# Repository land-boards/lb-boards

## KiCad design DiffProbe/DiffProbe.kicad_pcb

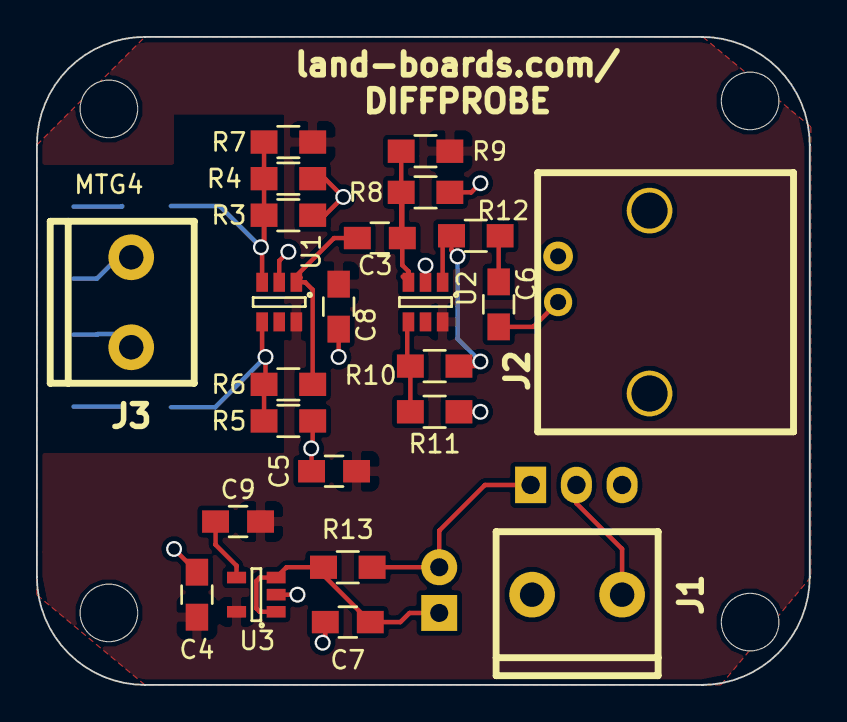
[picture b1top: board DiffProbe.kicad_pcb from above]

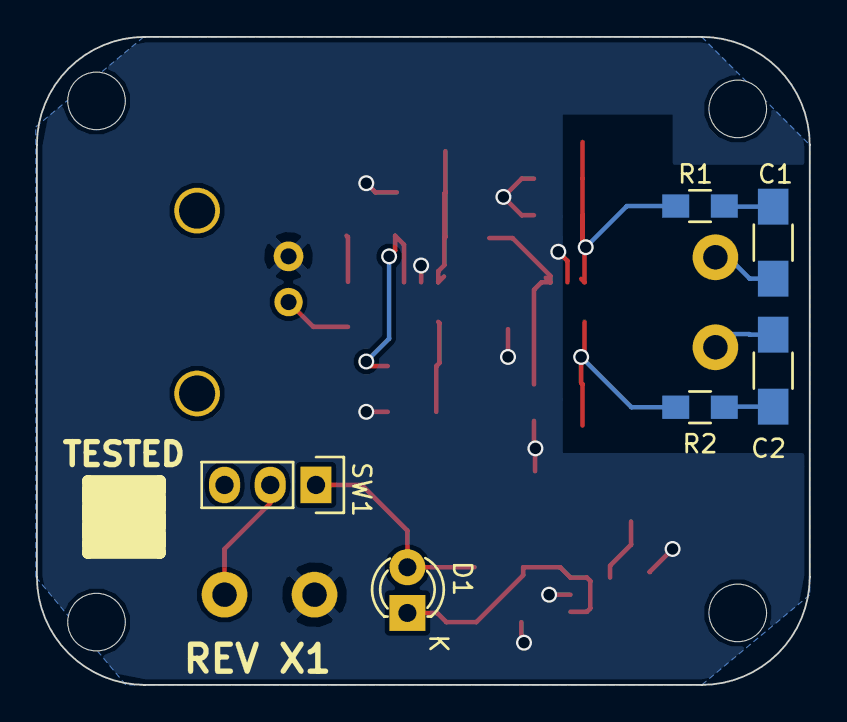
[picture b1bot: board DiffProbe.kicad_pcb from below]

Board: 2 copper layers, 42.9 x 36.0 mm, 35 parts (6 on the bottom side), 18 nets.

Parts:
C1, C2: 2.2nF/1kV; R_1206_HandSoldering
C3, C4, C5, C9: 10nF; C_0805_HandSoldering
C6, C7: 1uF; C_0805_HandSoldering
C8: 10uF; C_0805_HandSoldering
D1: LED; LED-3MM
J1, J3: CONN_01X02; TB2-5MM
J2: BNC; BNC-RT
MTG1, MTG2, MTG3, MTG4: MTG_HOLE; MountingHole_3.2mm_M3
R1, R2: 49.9K; R_0805_HandSoldering
R3, R5: 549; R_0805_HandSoldering
R4, R7, R8: 10K; R_0805_HandSoldering
R6: 4.99K; R_0805_HandSoldering
R9: 191K; R_0805_HandSoldering
R10: 499; R_0805_HandSoldering
R11: 54.9; R_0805_HandSoldering
R12: 48.7; R_0805_HandSoldering
R13: 75; R_0805_HandSoldering
SW1: SPST; Pin_Header_Straight_1x03
TESTED: TESTED_COUPON; TEST_BLK-REAR
U1, U2: LTC6268S6; SOT-23-6
U3: LT1761; SOT-23-5

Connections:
+5V: C4.1, C5.1, C8.1, C9.1, R7.2, R9.2, U1.6, U2.6, U3.5
GND: C4.2, C5.2, C7.2, C8.2, J1.2, J2.2, R3.2, R4.2, R5.1, R8.2, R11.1, U1.2, U2.2, U3.2
unnamed: C1.1, R1.2
unnamed: C1.2, J3.2
unnamed: C2.1, R2.2
unnamed: C2.2, J3.1
unnamed: C3.1, R8.1, R9.1, U2.3
unnamed: C3.2, R6.2, U1.1
unnamed: C6.1, J2.1
unnamed: C6.2, R12.2
unnamed: C7.1, D1.1, R13.1, U3.1, U3.3
unnamed: C9.2, U3.4
unnamed: D1.2, R13.2, SW1.1
unnamed: J1.1, SW1.2
unnamed: R1.1, R3.1, R4.1, R7.1, U1.3
unnamed: R2.1, R5.2, R6.1, U1.4
unnamed: R10.1, R11.2, U2.4
unnamed: R10.2, R12.1, U2.1

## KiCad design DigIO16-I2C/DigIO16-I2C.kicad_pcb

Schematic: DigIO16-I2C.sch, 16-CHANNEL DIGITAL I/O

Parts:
C1, C2: 0.1uF; C_Rect_L7_W2_P5
F1: FUSE; SM1206
FID1, FID2: ADAFRUIT_FIDUCIAL; FIDUCIAL
J1, J5: CONN_3; PIN_ARRAY_3X1
J2, J3: CONN_4; pin_array_4x1
J4: CONN_3X2; Pin_Header_Straight_2x03
J6: CONN_02X02; Pin_Header_Straight_2x02
J7: CONN_01X02; Pin_Header_Straight_1x02
J8: DB25; DB25FC
MTG1, MTG2, MTG3, MTG4: MTG_HOLE; MTG-6-32
R1, R2: 2.2K; R4-5
R3, R4, R6, R7, R8: 10K; R4-5
R5: 1K; R4-5
ST1, ST2: CONN_1; REV_BLOCK
U1: MCP23017P; DIP-28__300_ELL
U2: 24C01; DIP-8__300_ELL

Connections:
/A0: J4.6, R7.1, U1.15 (A0), U2.1 (A0)
/A1: J4.4, R8.1, U1.16 (A1), U2.2 (A1)
/A2: J4.2, R6.1, U1.17 (A2), U2.3 (A2)
/F5V: F1.2, J8.1, J8.2, J8.14
/INT: J5.2 (PM), R3.1, U1.20 (INTA)
/RST: R4.1, U1.18 (~RST)
/SCL: J2.4, J3.4, J6.4, U1.12 (SCL), U2.6 (SCL)
/SDA: J2.3, J3.3, J6.2, U1.13 (SDA), U2.5 (SDA)
/VCC: C1.1, C2.1, F1.1, J1.2 (PM), J2.2, J3.2, R1.2, R2.2, R3.2, R4.2, R5.2, R6.2, R7.2, R8.2, U1.9 (VDD), U2.8 (VCC)
GND: C1.2, C2.2, J1.1, J1.3, J2.1, J3.1, J4.1, J4.3, J4.5, J5.1, J5.3, J7.2, J8.7, J8.12, J8.13, J8.19, J8.20, J8.25, U1.10 (VSS), U2.4 (GND)
unnamed: J6.1, R1.1
unnamed: J6.3, R2.1
unnamed: J7.1, R5.1, U2.7 (TEST)
unnamed: J8.3, U1.27 (GPA6)
unnamed: J8.4, U1.25 (GPA4)
unnamed: J8.5, U1.23 (GPA2)
unnamed: J8.6, U1.21 (GPA0)
unnamed: J8.8, U1.1 (GPB0)
unnamed: J8.9, U1.3 (GPB2)
unnamed: J8.10, U1.5 (GPB4)
unnamed: J8.11, U1.7 (GPB6)
unnamed: J8.15, U1.28 (GPA7)
unnamed: J8.16, U1.26 (GPA5)
unnamed: J8.17, U1.24 (GPS3)
unnamed: J8.18, U1.22 (GPA1)
unnamed: J8.21, U1.2 (GPB1)
unnamed: J8.22, U1.4 (GPB3)
unnamed: J8.23, U1.6 (GPB5)
unnamed: J8.24, U1.8 (GPB7)

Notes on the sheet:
SCL SDA VCC GND
GND VCC GND
~CP ~INT GND
POWER
I2C

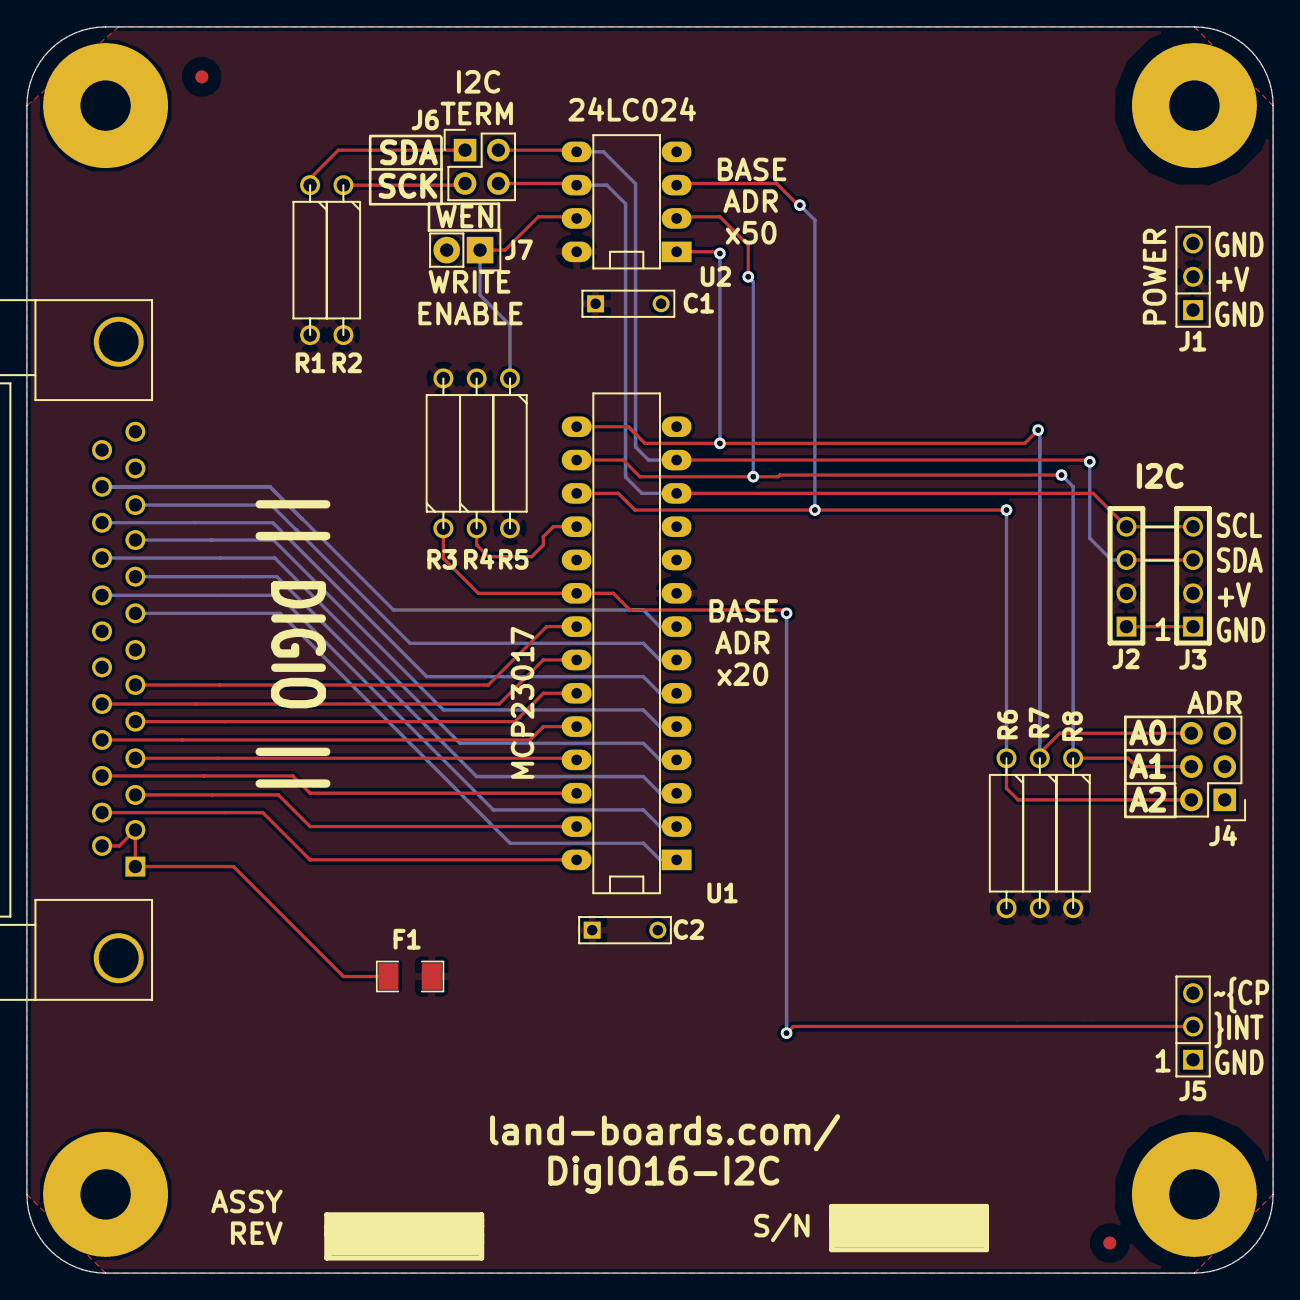
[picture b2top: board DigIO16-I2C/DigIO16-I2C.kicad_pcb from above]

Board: 2 copper layers, 95.0 x 95.0 mm, 30 parts (0 on the bottom side), 29 nets.

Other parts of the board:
TESTED: VAL**; TEST_BLK-REAR

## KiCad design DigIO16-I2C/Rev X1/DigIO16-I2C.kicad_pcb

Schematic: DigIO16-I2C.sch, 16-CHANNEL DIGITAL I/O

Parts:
F1: FUSE; SM1206
FID1, FID2: ADAFRUIT_FIDUCIAL; FIDUCIAL
HDR1: CONN_3X2; pin_array_3x2
J1: DB25; DB25FC
J2, J5: CONN_3; PIN_ARRAY_3X1
J3, J4: CONN_4; pin_array_4x1
MTG1, MTG2, MTG3, MTG4: MTG_HOLE; MTG-6-32
RP2: RR9; SIL-10
ST1, ST2: CONN_1; REV_BLOCK
U1: MCP23017P; DIP-28__300
U10: 24C01; DIP-8__300

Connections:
/A0: HDR1.6, RP2.6, U1.15 (A0), U10.1 (A0)
/A1: HDR1.4, RP2.5, U1.16 (A1), U10.2 (A1)
/A2: HDR1.2, RP2.4, U1.17 (A2), U10.3 (A2)
/SCL: J3.4, J4.4, U1.12 (SCL), U10.6 (SCL)
/SDA: J3.3, J4.3, U1.13 (SDA), U10.5 (SDA)
/VCC: F1.1, J2.2 (PM), J3.2, J4.2, RP2.1, U1.9 (VDD), U10.8 (VCC)
GND: HDR1.1, HDR1.3, HDR1.5, J1.7, J1.12, J1.13, J1.19, J1.20, J1.25, J2.1, J2.3, J3.1, J4.1, J5.1, J5.3, U1.10 (VSS), U10.4 (GND)
unnamed: J1.6, U1.21 (GPA0)
unnamed: RP2.3, U1.18 (~RST)
unnamed: J5.2 (PM), RP2.7, U1.19 (INTB), U1.20 (INTA)
unnamed: J1.11, U1.7 (GPB6)
unnamed: J1.23, U1.6 (GPB5)
unnamed: J1.10, U1.5 (GPB4)
unnamed: J1.22, U1.4 (GPB3)
unnamed: J1.9, U1.3 (GPB2)
unnamed: J1.21, U1.2 (GPB1)
unnamed: J1.8, U1.1 (GPB0)
unnamed: J1.15, U1.28 (GPA7)
unnamed: J1.3, U1.27 (GPA6)
unnamed: J1.16, U1.26 (GPA5)
unnamed: J1.4, U1.25 (GPA4)
unnamed: J1.17, U1.24 (GPS3)
unnamed: J1.5, U1.23 (GPA2)
unnamed: J1.18, U1.22 (GPA1)
unnamed: F1.2, J1.1, J1.2, J1.14
unnamed: J1.24, U1.8 (GPB7)

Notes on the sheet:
SCL SDA VCC GND
GND VCC GND
~CP ~INT GND
POWER
I2C

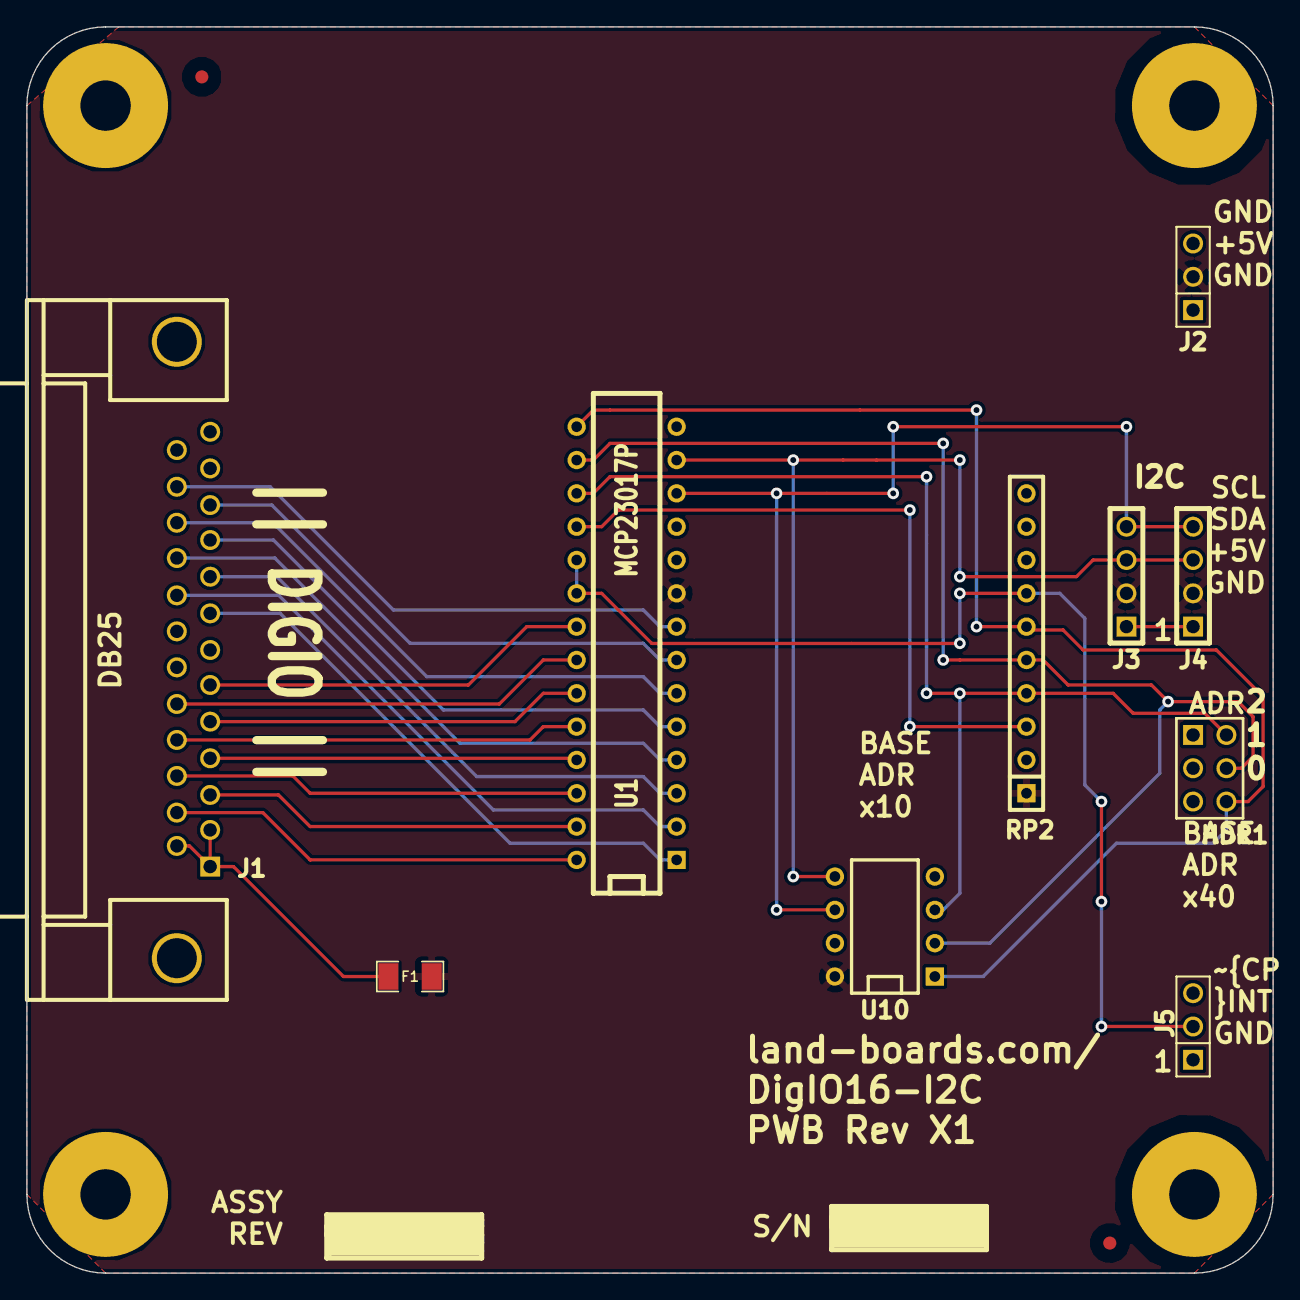
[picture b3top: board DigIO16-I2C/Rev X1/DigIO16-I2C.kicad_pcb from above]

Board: 2 copper layers, 95.0 x 95.0 mm, 18 parts (0 on the bottom side), 26 nets.

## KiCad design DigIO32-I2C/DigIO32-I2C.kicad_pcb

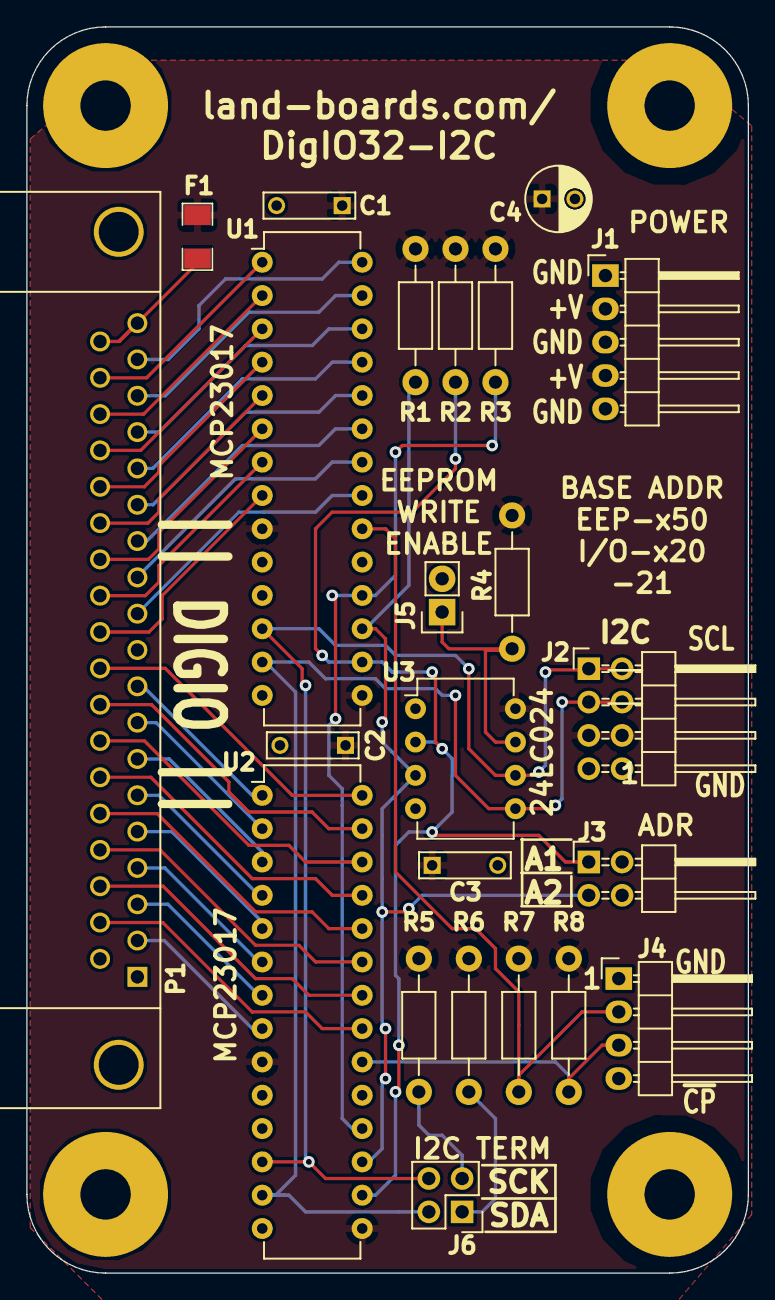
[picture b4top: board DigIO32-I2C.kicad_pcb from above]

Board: 2 copper layers, 55.0 x 95.0 mm, 28 parts (0 on the bottom side), 45 nets.

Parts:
C1, C2, C3: 0.1uF; C_Rect_L7_W2_P5
C4: 47uF; C_Radial_D5_L11_P2.5
F1: FUSE; SM1206
J1: CONN_01X05; Pin_Header_Angled_1x05
J2: CONN_02X04; Pin_Header_Angled_2x04
J3: CONN_02X02; Pin_Header_Angled_2x02
J4: CONN_01X04; Pin_Header_Angled_1x04
J5: CONN_01X02; Pin_Header_Straight_1x02
J6: CONN_02X02; Pin_Header_Straight_2x02
MTG1, MTG2, MTG3, MTG4: MTG_HOLE; MTG-6-32
P1: DB37; DB37FC
R1, R2, R3, R7, R8: 10K; Resistor_Horizontal_RM10mm
R4: 1K; Resistor_Horizontal_RM10mm
R5, R6: 2.2K; Resistor_Horizontal_RM10mm
TESTED: TESTED_COUPON; TEST_BLK-REAR
U1, U2: MCP23017P; DIP-28_W7.62mm
U3: 24C01; DIP-8_W7.62mm

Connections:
/A1: J3.1, R2.1, U1.16, U2.16, U3.2
/A2: J3.3, R1.1, U1.17, U2.17, U3.3
/F5V: F1.2, P1.19, P1.37
/INT0: J4.3, R8.1, U2.20
/INT1: J4.2, R7.1, U1.20
/RST: R3.1, U1.18, U2.18
/SCL: J2.1, J2.2, J6.4, U1.12, U2.12, U3.6
/SDA: J2.3, J2.4, J6.2, U1.13, U2.13, U3.5
/VCC: C1.1, C2.1, C3.1, C4.1, F1.1, J1.2, J1.4, J2.5, J2.6, R1.2, R2.2, R3.2, R4.2, R5.2, R6.2, R7.2, R8.2, U1.9, U1.15, U2.9, U2.15, U3.8
GND: C1.2, C2.2, C3.2, C4.2, J1.1, J1.3, J1.5, J2.7, J2.8, J3.2, J3.4, J4.1, J4.4, J5.2, P1.1, P1.20, U1.10, U2.10, U3.4
unnamed: J5.1, R4.1, U3.7
unnamed: J6.1, R6.1
unnamed: J6.3, R5.1
unnamed: P1.2, U2.8
unnamed: P1.3, U2.7
unnamed: P1.4, U2.6
unnamed: P1.5, U2.5
unnamed: P1.6, U2.4
unnamed: P1.7, U2.3
unnamed: P1.8, U2.2
unnamed: P1.9, U2.1
unnamed: P1.11, U1.21
unnamed: P1.12, U1.22
unnamed: P1.13, U1.23
unnamed: P1.14, U1.24
unnamed: P1.15, U1.25
unnamed: P1.16, U1.26
unnamed: P1.17, U1.27
unnamed: P1.18, U1.28
unnamed: P1.21, U2.21
unnamed: P1.22, U2.22
unnamed: P1.23, U2.23
unnamed: P1.24, U2.24
unnamed: P1.25, U2.25
unnamed: P1.26, U2.26
unnamed: P1.27, U2.27
unnamed: P1.28, U2.28
unnamed: P1.29, U1.8
unnamed: P1.30, U1.7
unnamed: P1.31, U1.6
unnamed: P1.32, U1.5
unnamed: P1.33, U1.4
unnamed: P1.34, U1.3
unnamed: P1.35, U1.2
unnamed: P1.36, U1.1

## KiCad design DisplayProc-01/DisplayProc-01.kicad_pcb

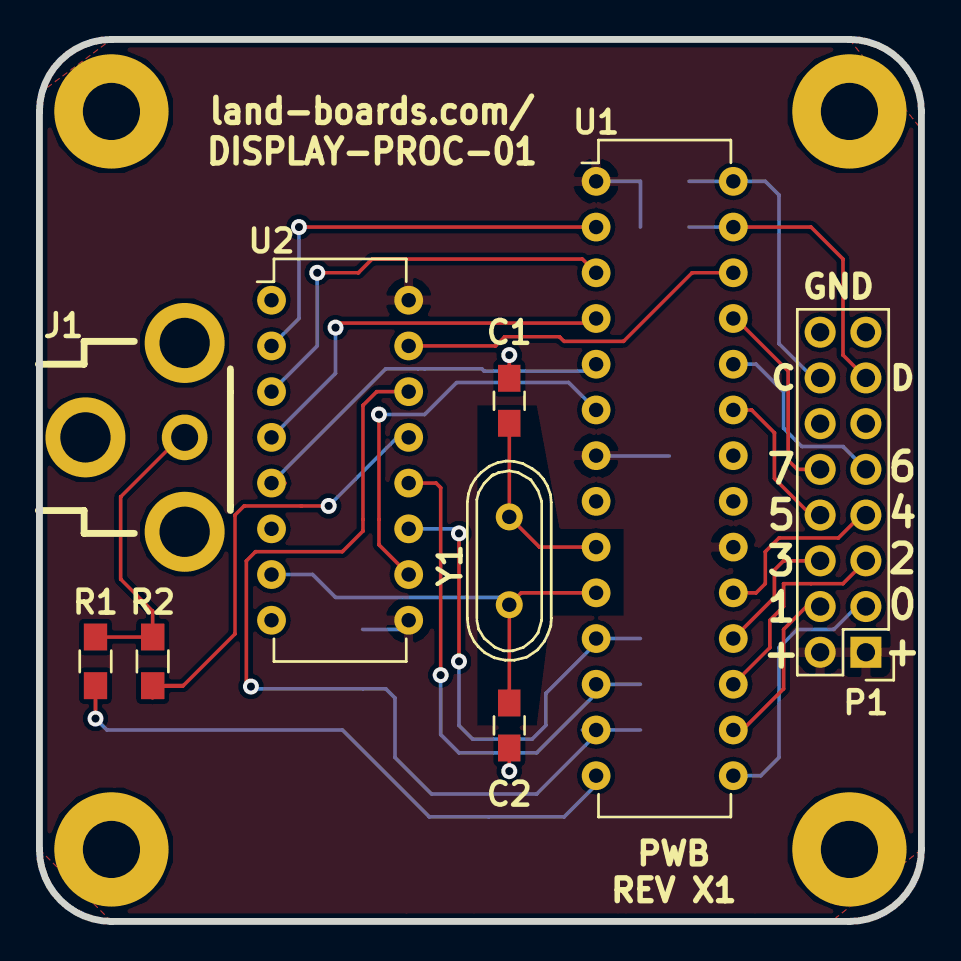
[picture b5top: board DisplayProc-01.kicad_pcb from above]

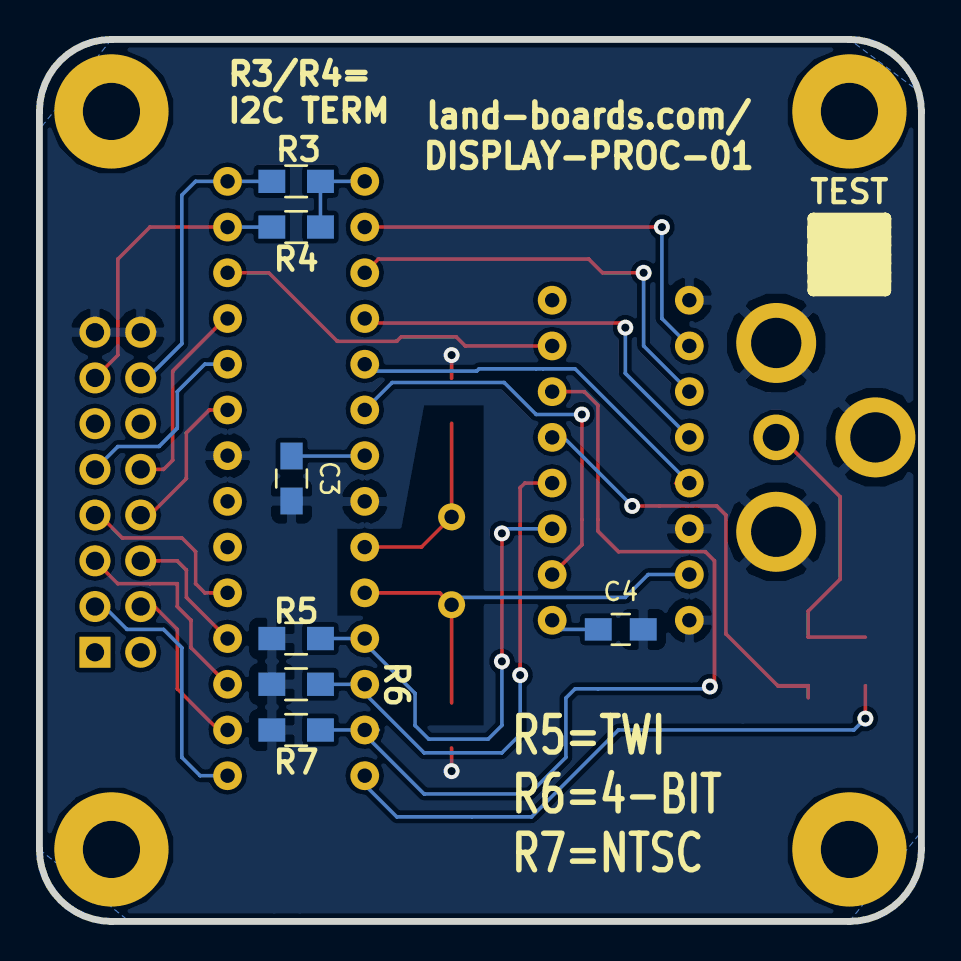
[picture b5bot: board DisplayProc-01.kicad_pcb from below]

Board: 2 copper layers, 49.0 x 49.0 mm, 21 parts (7 on the bottom side), 26 nets.

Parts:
C1, C2: 22pF; C_0805_HandSoldering
C3, C4: 0.1uF; C_0805_HandSoldering
J1: RCA-JACK; RCA
MTG1, MTG2, MTG3, MTG4: CONN_1; MTG-4-40
P1: CONN_02X08; Pin_Header_Straight_2x08
R1, R2: 470; R_0805_HandSoldering
R3, R4: OPEN; R_0805_HandSoldering
R5, R6, R7: 10K; R_0805_HandSoldering
TEST: COUPON; TEST_BLK-REAR
U1: ATMEGA328-PU; DIP-28_W7.62mm
U2: 74HCT166; DIP-16_W7.62mm
Y1: 16MHz; Crystal_HC49-U_Vertical

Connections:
/ACKSDA: P1.13, R4.1, U1.27
/AVAILSCL: P1.14, R3.2, U1.28
/ID0: P1.3, U1.15
/ID1: P1.4, U1.16
/ID2: P1.5, U1.17
/ID3: P1.6, U1.18
/ID4: P1.7, U1.19
/ID5: P1.8, U1.23
/ID6: P1.9, U1.24
/ID7: P1.10, U1.25
/VD0: U1.2, U2.2
/VD1: U1.3, U2.3
/VD2: U1.4, U2.4
/VD3: U1.5, U2.5
/VD4: U1.6, U2.10
/VD5: R5.1, U1.11, U2.11
/VD6: R6.1, U1.12, U2.12
/VD7: R7.1, U1.13, U2.14
/~LD: U1.26, U2.15
GND: C1.2, C2.2, C3.2, C4.2, J1.1, J1.2, J1.3, P1.15, P1.16, R5.2, R6.2, R7.2, U1.8, U1.22, U2.1, U2.6, U2.8
unnamed: C1.1, U1.9, Y1.2
unnamed: C2.1, U1.10, U2.7, Y1.1
unnamed: J1.4, R1.1, R2.1
unnamed: R1.2, U1.14
unnamed: R2.2, U2.13
VCC: C3.1, C4.1, P1.1, P1.2, R3.1, R4.2, U1.1, U1.7, U1.20, U2.9, U2.16

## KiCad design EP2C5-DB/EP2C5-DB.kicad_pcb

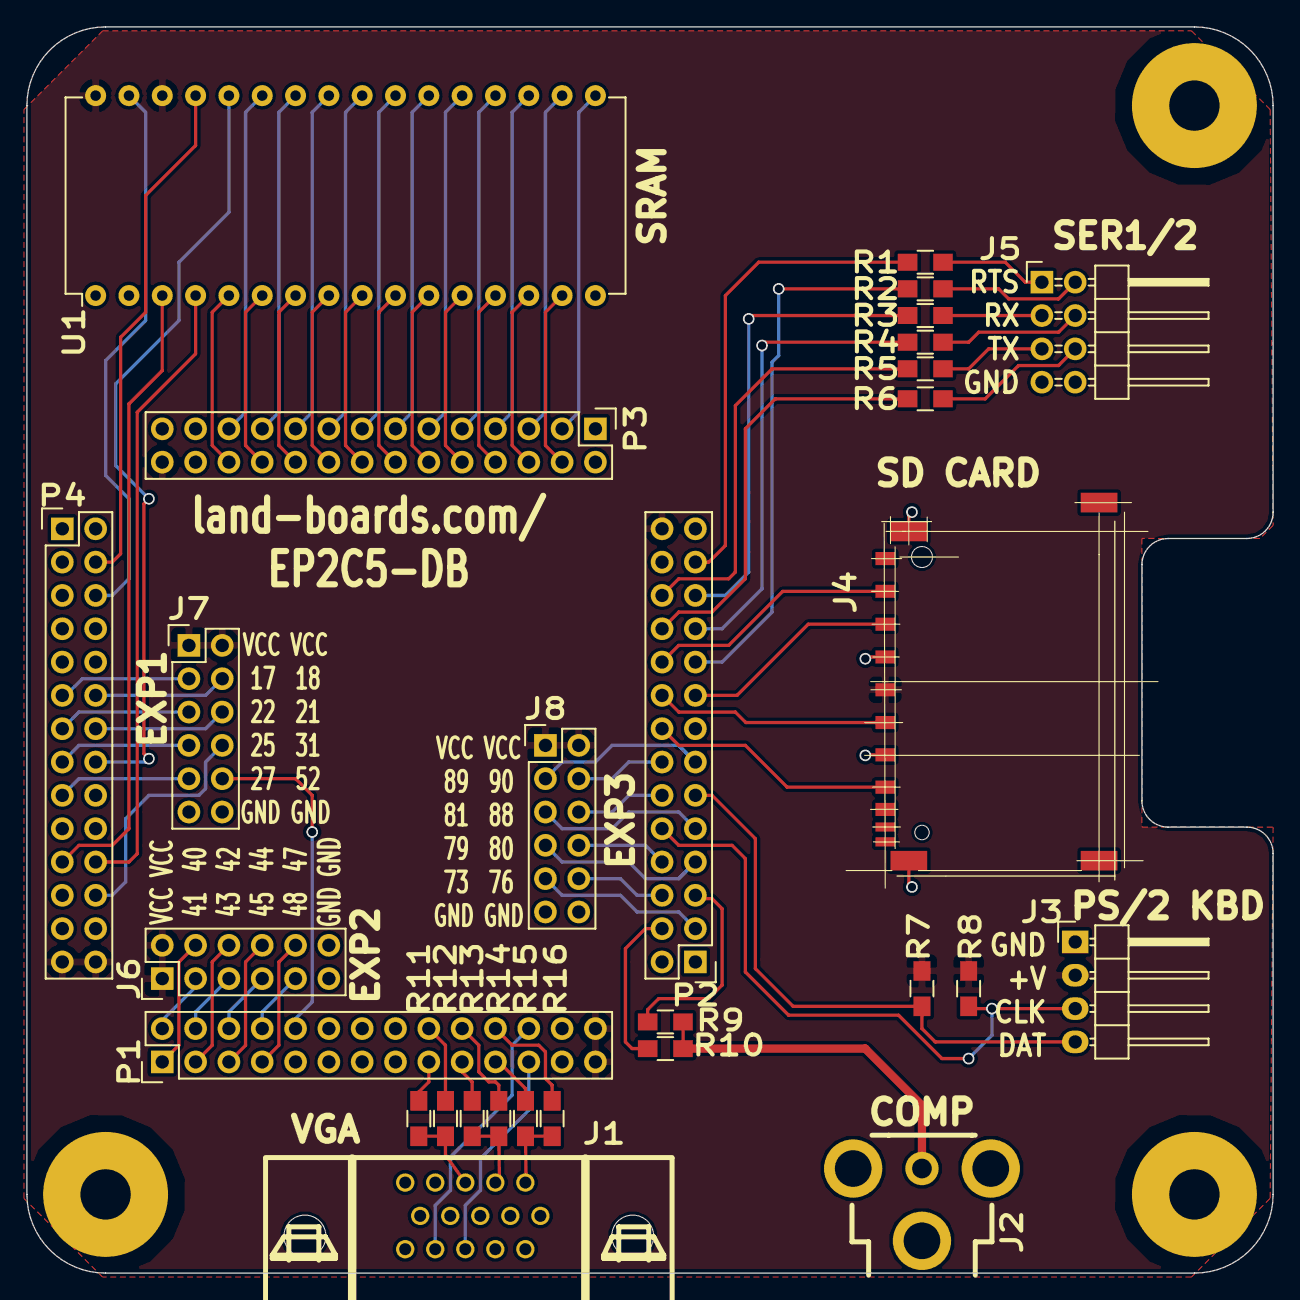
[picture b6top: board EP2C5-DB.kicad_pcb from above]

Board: 2 copper layers, 95.0 x 95.0 mm, 32 parts (0 on the bottom side), 85 nets.

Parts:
J1: VGA; DB_15F-VGA-fixed
J2: RCA-JACK; RCA
J3: CONN_01X04; Pin_Header_Angled_1x04
J4: SD_Card; SD_CARD
J5: CONN_02X04; Pin_Header_Angled_2x04
J6, J7, J8: CONN_02X06; Pin_Header_Straight_2x06
MTG1, MTG2, MTG3: MTG_HOLE; MTG-6-32
P1, P2, P3, P4: CONN_02X14; Pin_Header_Straight_2x14
R1, R2, R3, R4, R5, R6: 2.7K; R_0805_HandSoldering
R7, R8: 10K; R_0805_HandSoldering
R9, R11, R13, R15: 470; R_0805_HandSoldering
R10: 1K; R_0805_HandSoldering
R12, R14, R16: 680; R_0805_HandSoldering
U1: AS6C1008; DIP-32_W15.24mm

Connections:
/P4: P4.4, U1.29
/P8: P4.6, U1.31
/P17: J7.3, P4.11
/P18: J7.4, P4.12
/P21: J7.6, P4.14
/P22: J7.5, P4.13
/P24: P4.16, U1.28
/P25: J7.7, P4.15
/P27: J7.9, P4.17
/P28: P4.22, U1.4
/P30: P4.21, U1.3
/P31: J7.8, P4.24
/P40: J6.4, P1.1
/P41: J6.3, P1.2
/P42: J6.6, P1.3
/P43: J6.5, P1.4
/P44: J6.8, P1.5
/P45: J6.7, P1.6
/P47: J6.10, P1.7
/P48: J6.9, P1.8
/P52: J7.10, P1.10
/P63: P1.17, R11.1
/P64: P1.18, R12.1
/P65: P1.19, R13.1
/P67: P1.20, R14.1
/P69: P1.21, R15.1
/P70: P1.22, R16.1
/P71: J1.13, P1.23
/P72: J1.14, P1.24
/P73: J8.9, P2.3
/P74: P2.4, R10.1
/P75: P2.5, R9.1
/P76: J8.10, P2.6
/P79: J8.7, P2.7
/P80: J8.8, P2.8
/P81: J8.5, P2.9
/P86: J3.3, P2.10, R8.2
/P87: J3.4, P2.11, R7.2
/P88: J8.6, P2.12
/P89: J8.3, P2.13
/P90: J8.4, P2.14
/P92: J4.7, P2.16
/P93: J4.2, P2.17
/P94: J4.5, P2.18
/P96: P2.19, R2.2
/P97: J4.1, P2.20
/P99: P2.21, R4.2
/P100: P2.22, R6.2
/P101: P2.23, R3.1
/P103: P2.24, R5.1
/P104: P2.25, R1.1
/P112: P3.3, U1.17
/P113: P3.4, U1.15
/P114: P3.5, U1.18
/P115: P3.6, U1.14
/P118: P3.7, U1.19
/P119: P3.8, U1.13
/P120: P3.9, U1.20
/P121: P3.10, U1.12
/P122: P3.11, U1.21
/P125: P3.12, U1.11
/P126: P3.13, U1.22
/P129: P3.14, U1.10
/P132: P3.15, U1.23
/P133: P3.16, U1.9
/P134: P3.17, U1.24
/P135: P3.18, U1.8
/P136: P3.19, U1.25
/P137: P3.20, U1.7
/P139: P3.21, U1.26
/P141: P3.22, U1.6
/P142: P3.23, U1.27
/P143: P3.24, U1.5
/RTS1: J5.1, R1.2
/RTS2: J5.2, R2.1
/RX1: J5.3, R3.2
/RX2: J5.4, R4.1
/TX1: J5.5, R5.2
/TX2: J5.6, R6.1
GND: J1.5, J1.6, J1.7, J1.8, J1.10, J2.1, J2.2, J2.3, J3.1, J4.3, J4.6, J4.12, J4.13, J5.7, J5.8, J6.11, J6.12, J7.11, J7.12, J8.11, J8.12, P1.25, P1.26, P2.1, P2.2, P2.26, P2.27, P3.1, P3.2, P3.26, P3.27, P4.1, P4.2, P4.8, P4.9, P4.10, P4.25, P4.26, U1.2, U1.16
unnamed: J1.1, R15.2, R16.2
unnamed: J1.2, R13.2, R14.2
unnamed: J1.3, R11.2, R12.2
unnamed: J2.4, R9.2, R10.2
VCC: J3.2, J4.4, J6.1, J6.2, J7.1, J7.2, J8.1, J8.2, P1.27, P1.28, P2.28, P3.28, P4.27, P4.28, R7.1, R8.1, U1.30, U1.32

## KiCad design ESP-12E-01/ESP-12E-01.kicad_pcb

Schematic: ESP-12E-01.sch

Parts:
C1: 22uF; R_1210_HandSoldering
C2, C3: 0.1uF; R_0805_HandSoldering
C4: 0.1uF; C_0805_HandSoldering
J1: DCJ0202; DCJ-NEW
MTG1, MTG2, MTG3, MTG4: CONN_1; MTG-4-40
P1: FTDI-3.3V; Pin_Header_Angled_1x06
P2, P3, P4, P5, P6, P7, P8, P9, P10: CONN_01X03; Pin_Header_Straight_1x03
P11: CONN_01X04; Pin_Header_Straight_1x04
Q1, Q2: 2N3904; SOT-23_Handsoldering
R1, R2, R3, R6, R7, R8: 10K; R_0805_HandSoldering
R4: DNP; R_0805_HandSoldering
R5: 3.3K; R_0805_HandSoldering
TEST1: COUPON; TEST_BLK-REAR
U1: ESP-12E-sides; ESP-12E
U2: AP1117-3.3V; SOT-223

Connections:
+3V3: C1.1, C3.1, P2.2, P3.2, P4.2, P5.2, P6.2, P7.2, P8.2, P9.2, P10.2, P11.2, R2.2, R3.2, R4.2, R5.2, R6.2, U1.8 (VCC), U2.2 (VO), U2.4 (VO)
+9V: C2.1, J1.1, U2.3 (VIN)
/ADC: P2.3, U1.2 (ADC)
/CH_PD: R5.1, U1.3 (CH_PD)
/CTS: P1.2 (CTS), Q2.1, R7.1
/ESPRXD: P1.4 (TX), U1.21 (RXD)
/ESPTXD: P1.5 (RX), U1.22 (TXD)
/GPIO0: Q2.3, R3.1, U1.18 (GPIO0)
/GPIO2: P10.3, R2.1, U1.17 (GPIO2)
/GPIO4: P11.3, U1.19 (GPIO4)
/GPIO5: P11.4, U1.20 (GPIO5)
/GPIO9: P7.3, U1.11 (GPIO9)
/GPIO10: P8.3, U1.12 (GPIO10)
/GPIO12: P5.3, U1.6 (GPIO12)
/GPIO13: P6.3, U1.7 (GPIO13)
/GPIO14: P4.3, U1.5 (GPIO14)
/GPIO15: P9.3, R1.2, U1.16 (GPIO15)
/GPIO16: P3.3, R4.1, U1.4 (GPIO16)
/RST: C4.2, Q1.3, R6.1, U1.1 (REST)
/RTS: P1.6 (RTS), Q1.1, R8.1
GND: C1.2, C2.2, C3.2, C4.1, J1.2, J1.3, P1.1 (GND), P2.1, P3.1, P4.1, P5.1, P6.1, P7.1, P8.1, P9.1, P10.1, P11.1, R1.1, U1.15 (GND), U2.1 (GND)
unnamed: Q1.2, R7.2
unnamed: Q2.2, R8.2

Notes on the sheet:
VOLTAGE REGULATOR

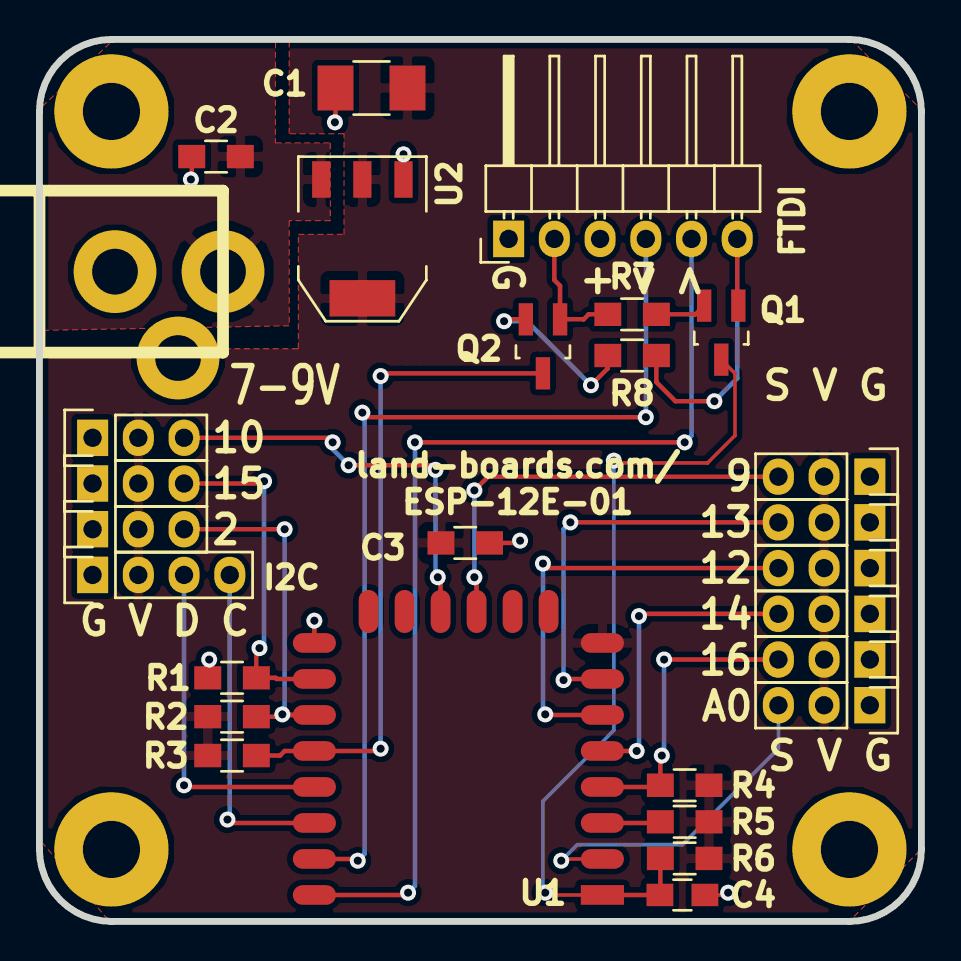
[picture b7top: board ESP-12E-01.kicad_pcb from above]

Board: 2 copper layers, 49.0 x 49.0 mm, 34 parts (0 on the bottom side), 23 nets.

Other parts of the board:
TEST: COUPON; TEST_BLK-REAR
